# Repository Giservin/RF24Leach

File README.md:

This LEACH prioritize energy to pick the next cluster head. The node that use the smallest energy will be picked to be a cluster head for the next round.

## Libraries
Install these libraries in your Arduino library folder

* https://github.com/nRF24/RF24
* https://github.com/nRF24/RF24Network
* https://github.com/adafruit/Adafruit_BusIO
* https://github.com/adafruit/Adafruit_NeoPixel
* https://github.com/adafruit/Adafruit-GFX-Library
* https://github.com/adafruit/Adafruit_SSD1306
* https://github.com/adafruit/Adafruit_INA219
* http://www.rinkydinkelectronics.com/library.php?id=73

## Note
For RF24Network Library Sleep Function to work, it must be manually enabled by uncommenting the `#define ENABLE_SLEEP_MODE` in `RF24Network_config.h`

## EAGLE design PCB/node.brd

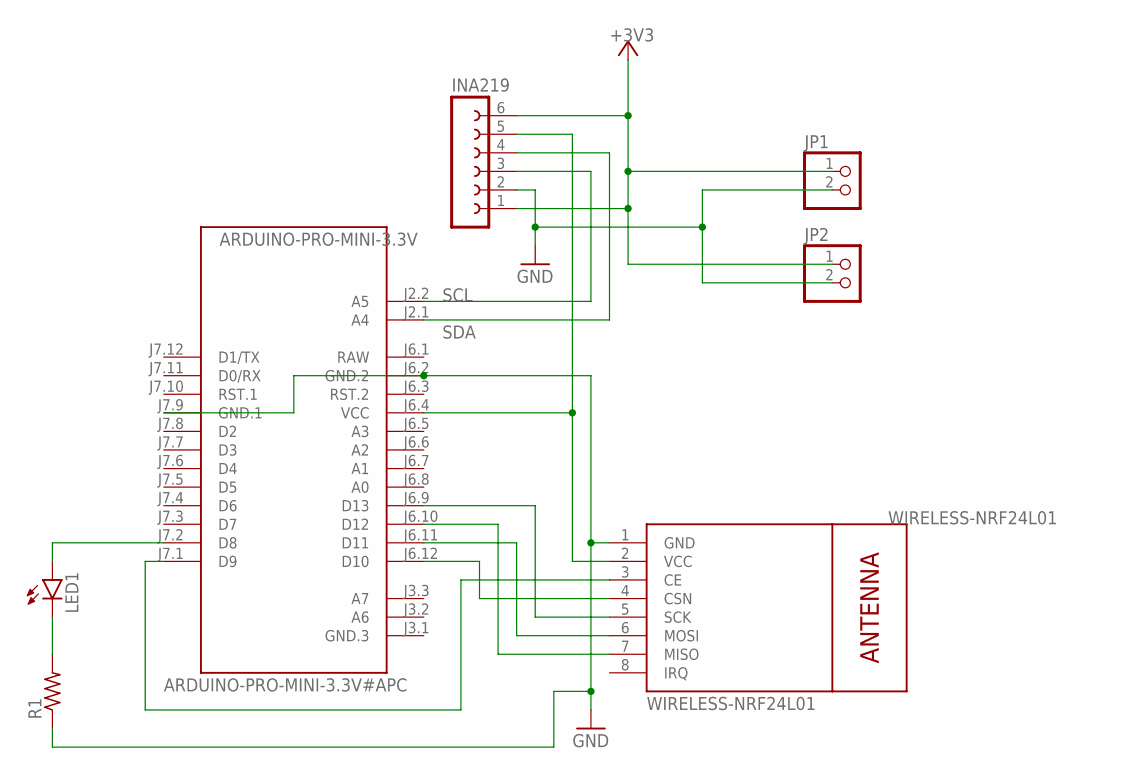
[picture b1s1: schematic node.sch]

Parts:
ARDUINO-PRO-MINI-3.3V: ARDUINO-PRO-MINI-3.3V#APC; ARDUINO-PRO-MINI#APC
INA219: FE06-1; FE06
JP1, JP2: PINHD-1X2; 1X02
LED1: LED3MM
R1: R-US_0204/7; 0204/7
WIRELESS-NRF24L01: WIRELESS-NRF24L01

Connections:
+3V3: INA219.1, INA219.6, JP1.1, JP2.1
GND: ARDUINO-PRO-MINI-3.3V.J6.2 (GND.2), ARDUINO-PRO-MINI-3.3V.J7.9 (GND.1), INA219.2, JP1.2, JP2.2, R1.1, WIRELESS-NRF24L01.1 (GND)
unnamed: ARDUINO-PRO-MINI-3.3V.J7.2 (D8), LED1.A
unnamed: LED1.K (C), R1.2
unnamed: ARDUINO-PRO-MINI-3.3V.J6.4 (VCC), INA219.5, WIRELESS-NRF24L01.2 (VCC)
unnamed: ARDUINO-PRO-MINI-3.3V.J6.12 (D10), WIRELESS-NRF24L01.4 (CSN)
unnamed: ARDUINO-PRO-MINI-3.3V.J7.1 (D9), WIRELESS-NRF24L01.3 (CE)
unnamed: ARDUINO-PRO-MINI-3.3V.J6.9 (D13), WIRELESS-NRF24L01.5 (SCK)
unnamed: ARDUINO-PRO-MINI-3.3V.J6.11 (D11), WIRELESS-NRF24L01.6 (MOSI)
unnamed: ARDUINO-PRO-MINI-3.3V.J6.10 (D12), WIRELESS-NRF24L01.7 (MISO)
RAW: ARDUINO-PRO-MINI-3.3V.J6.1 (RAW)
SCL: ARDUINO-PRO-MINI-3.3V.J2.2 (A5), INA219.3
SDA: ARDUINO-PRO-MINI-3.3V.J2.1 (A4), INA219.4

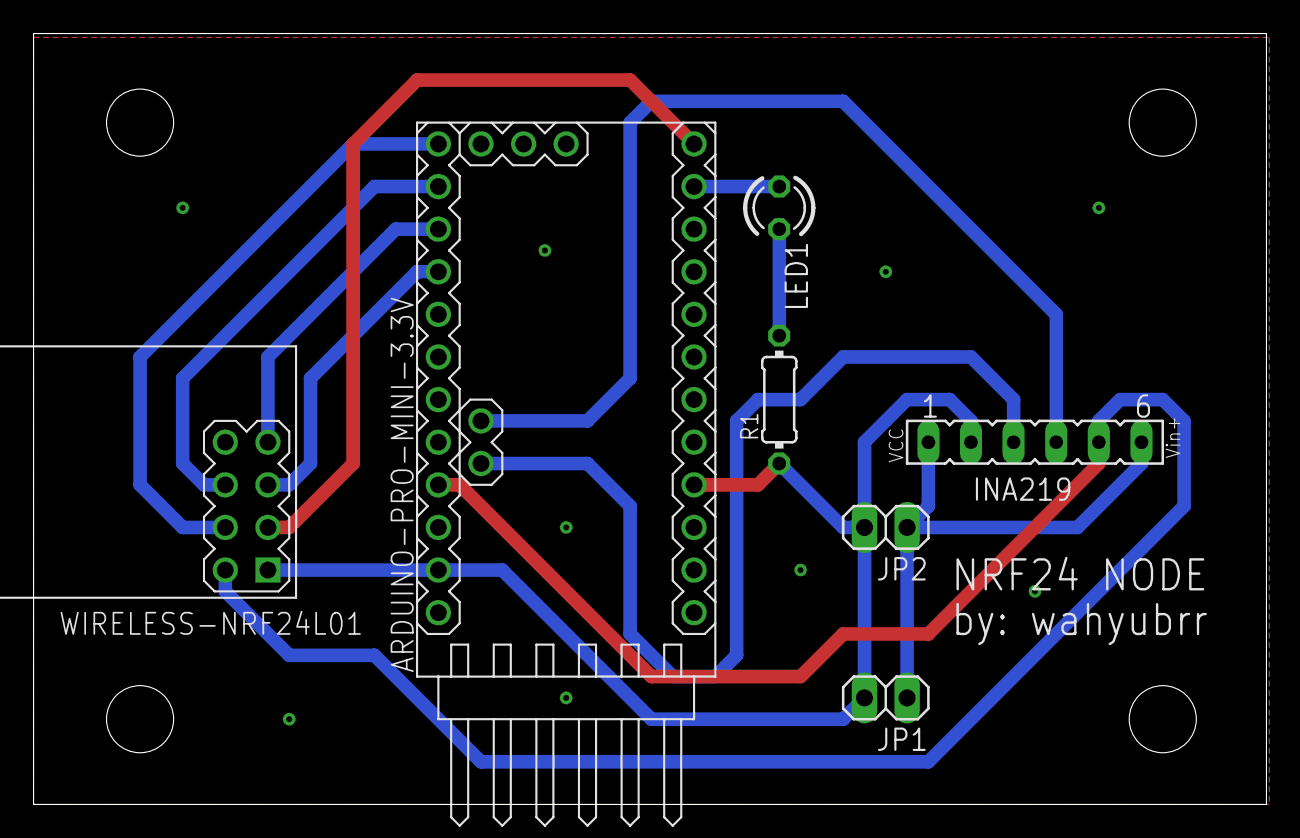
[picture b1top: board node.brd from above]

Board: 2 copper layers, 73.5 x 46.0 mm, 7 parts (0 on the bottom side), 12 nets.

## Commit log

2020-11-21 Connecting all nodes
2020-11-24 cluster head exchange with two nodes
2020-11-24 switching cluster head tested with 5 nodes
2020-11-24 more stable 5 node, tested overnight
2020-12-01 added sleep mode
2020-12-02 - packets_sent incremented if packet arrived to destination - adding timeout last_try when cluster head is sending to other node
2020-12-02 - adding rtc and status
2020-12-02 - adding current sensing - adding avg_current in struct, both base station and node
2020-12-07 init
2020-12-07 -still one cluster, but already stable enough
2020-12-08 -Exchanging cluster head with 10 nodes and 2 CHs -Tested for almost 2 hours and still going strong -Not yet implementing LEACH
2020-12-09 -Added LEACH -firmware already stable
2020-12-09 removing redundant files
2020-12-15 sleep revamped
2020-12-15 still bugged
2020-12-15 successful sleeping
2021-03-30 fix the communication issue with power level
2021-04-02 still testing, no major change
2021-04-13 finally a seamless run for the entire night
2021-04-13 deleted experimental files
2021-04-13 initialized static clustering
2021-04-14 few bugfixes, now stable
2021-04-14 fixed timing
2021-05-21 initialized with simple transmission time formula with millis()
2021-05-21 implemented basic transmission time to nodes
2021-06-02 clean discovery feature
2021-06-02 added some patch and failsafe to make the process smoother
2021-06-02 bersih2 kodingan
2021-07-06 considering energy to pick next cluster head
2021-07-06 This is a pure form of LEACH
2021-07-06 This leach consider energy to pick a cluster head
2021-10-27 Added PCB's file

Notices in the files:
parts and their libraries:
diy-modules: Released under the Creative Commons Attribution 4.0 International License: http://creativecommons.org/licenses/by/4.0
